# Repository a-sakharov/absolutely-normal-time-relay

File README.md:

# Очень лабораторный таймер

Все это к статье https://habr.com/ru/articles/726276/

 - firmware - прошивка MCS-48 (листинг, исходник, HEX)
 - schematics - схема самого таймера (без трассировки, конечно)
 - schematics_programmer - схема прошивальщика (есть непроверенные изменения!)

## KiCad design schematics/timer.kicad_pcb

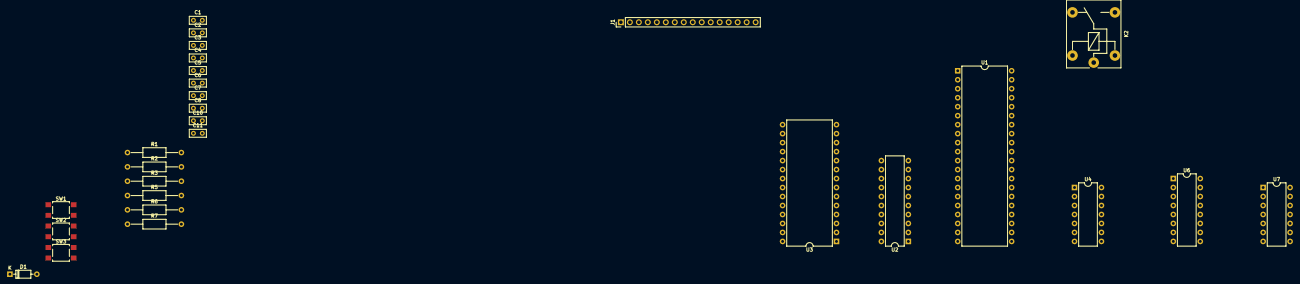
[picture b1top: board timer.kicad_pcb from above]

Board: 2 copper layers, 28 parts (0 on the bottom side), 44 nets, no tracks yet.

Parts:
C1, C2, C3, C4, C5, C6, C7, C8, C10, C11: 1uF; C_Rect_L4.6mm_W2.0mm_P2.50mm_MKS02_FKP02
D1: 1N4148; D_DO-35_SOD27_P7.62mm_Horizontal
J1: Conn_01x16_Pin; PinHeader_1x16_P2.54mm_Vertical
K2: FINDER-36.11; Relay_SPDT_Finder_36.11
R1, R2, R3, R5, R6, R7: 4.7k; R_Axial_DIN0207_L6.3mm_D2.5mm_P15.24mm_Horizontal
SW1, SW2, SW3: SW_Push; SW_SPST_TL3305C
U1: 8035; DIP-40_W15.24mm
U2: 74LS377; DIP-20_W7.62mm
U3: DIP-28_W15.24mm
U4: 74HC14; DIP-14_W7.62mm
U6: 4043; DIP-16_W7.62mm
U7: 4013; DIP-14_W7.62mm

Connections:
+5V: C2.2, C3.1, C4.1, C7.1, C8.2, J1.2, J1.15, R1.1, R2.2, R3.2, U1.7 (EA), U1.26 (VDD), U1.40 (VCC), U2.20 (VCC), U3.27 (~WE), U3.28 (VCC), U4.14 (VCC), U6.5 (EN), U6.16 (Vdd), U7.5 (D), U7.14 (VDD)
/ADDR8: U1.21 (P2.0), U3.25 (A8)
/ADDR9: U1.22 (P2.1), U3.24 (A9)
/ADDR10: U1.23 (P2.2), U3.21 (A10)
/ADDR11: U1.24 (P2.3), U3.23 (A11)
/ADDR_DATA0: U1.12 (DB.0), U2.3 (D0), U3.11 (D0)
/ADDR_DATA1: U1.13 (DB.1), U2.4 (D1), U3.12 (D1)
/ADDR_DATA2: U1.14 (DB.2), U2.7 (D2), U3.13 (D2)
/ADDR_DATA3: U1.15 (DB.3), U2.8 (D3), U3.15 (D3)
/ADDR_DATA4: U1.16 (DB.4), U2.13 (D4), U3.16 (D4)
/ADDR_DATA5: U1.17 (DB.5), U2.14 (D5), U3.17 (D5)
/ADDR_DATA6: U1.18 (DB.6), U2.17 (D6), U3.18 (D6)
/ADDR_DATA7: U1.19 (DB.7), U2.18 (D7), U3.19 (D7)
/ALE: U1.11 (ALE), U4.1
/BTN1: U1.1 (T0), U4.6
/BTN2: U1.39 (T1), U4.4
/DISP_D4: J1.11, U1.27 (P1.0)
/DISP_D5: J1.12, U1.28 (P1.1)
/DISP_D6: J1.13, U1.29 (P1.2)
/DISP_D7: J1.14, U1.30 (P1.3)
/DISP_E: J1.6, U1.32 (P1.5)
/DISP_RS: J1.4, U1.31 (P1.4)
/PSEN: U1.9 (~PSEN), U3.22 (~OE)
/SS: U1.5 (~SS), U7.1 (Q)
/SS_BTN: U6.2, U7.3 (C)
/nALE: U2.11 (CP), U4.2, U7.4 (R)
GND: C1.1, C2.1, C3.2, C4.2, C5.1, C6.1, C7.2, C8.1, C10.2, C11.2, D1.2 (A), J1.1, J1.5, J1.7, J1.8, J1.9, J1.10, J1.16, K2.A1, R5.2, R6.2, R7.2, SW1.1, SW2.1, SW3.1, U1.20 (GND), U2.1 (~E), U2.10 (GND), U3.2 (A12), U3.14 (GND), U3.20 (~CE), U4.7 (GND), U6.8 (Vss), U7.7 (VSS)
unnamed: C10.1, R2.1, SW1.2, U4.5
unnamed: C11.1, R3.1, SW3.2, U4.3
unnamed: D1.1 (K), K2.A2
unnamed: R5.1, U6.3
unnamed: R6.1, U6.4
unnamed: C5.2, U1.2 (X1)
unnamed: C6.2, U1.3 (X2)
unnamed: C1.2, R1.2, SW2.2, U1.4 (~RESET)
unnamed: U2.2 (Q0), U3.10 (A0)
unnamed: U2.5 (Q1), U3.9 (A1)
unnamed: U2.6 (Q2), U3.8 (A2)
unnamed: U2.9 (Q3), U3.7 (A3)
unnamed: U2.12 (Q4), U3.6 (A4)
unnamed: U2.15 (Q5), U3.5 (A5)
unnamed: U2.16 (Q6), U3.4 (A6)
unnamed: U2.19 (Q7), U3.3 (A7)
unnamed: R7.1, U7.6 (S)

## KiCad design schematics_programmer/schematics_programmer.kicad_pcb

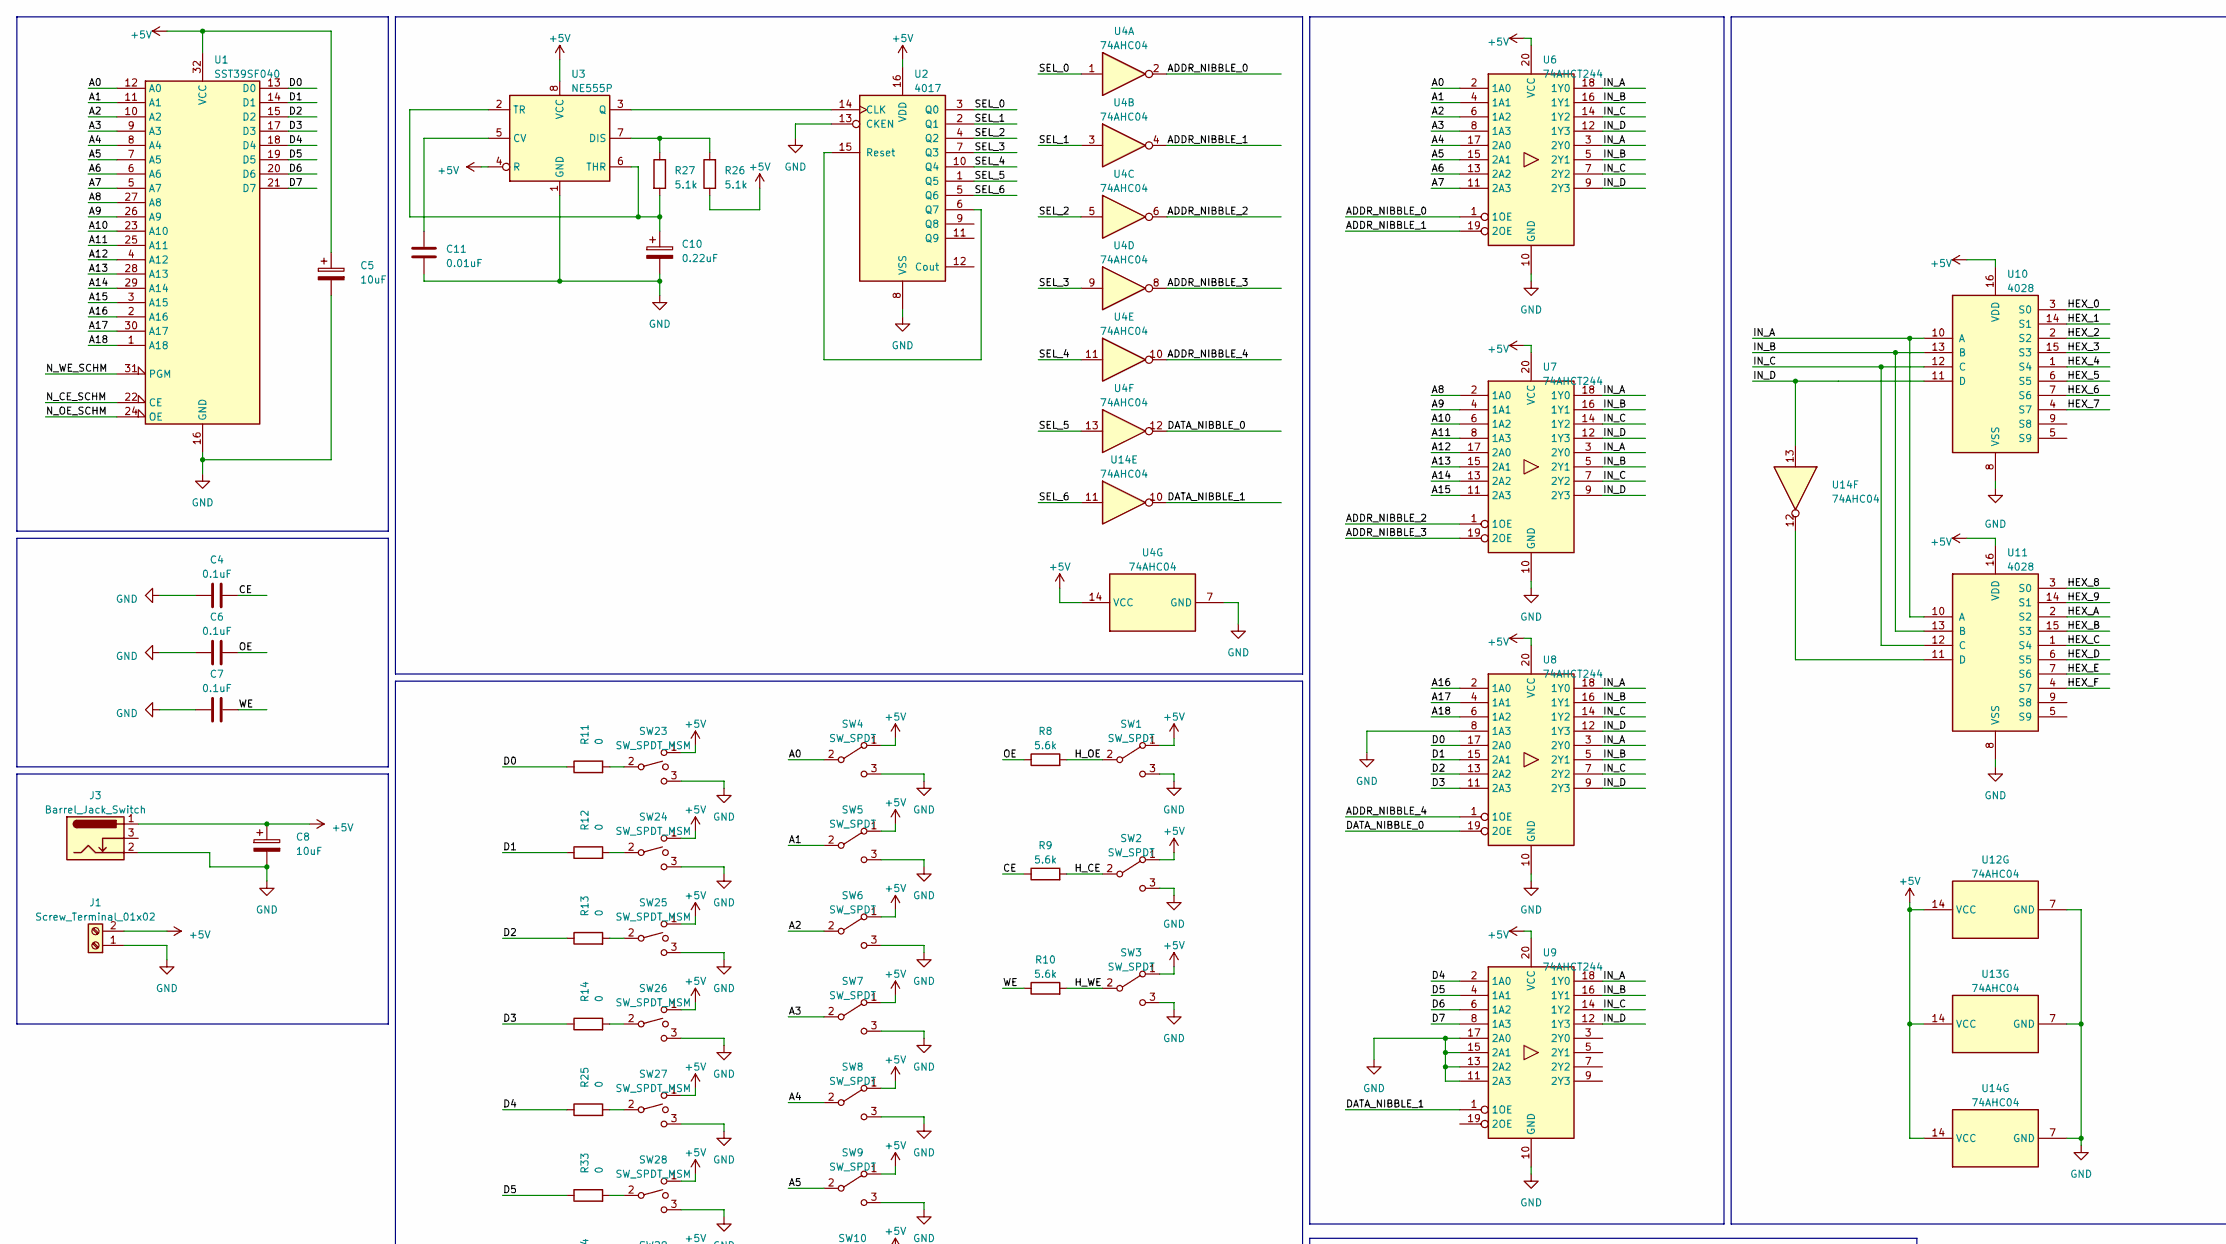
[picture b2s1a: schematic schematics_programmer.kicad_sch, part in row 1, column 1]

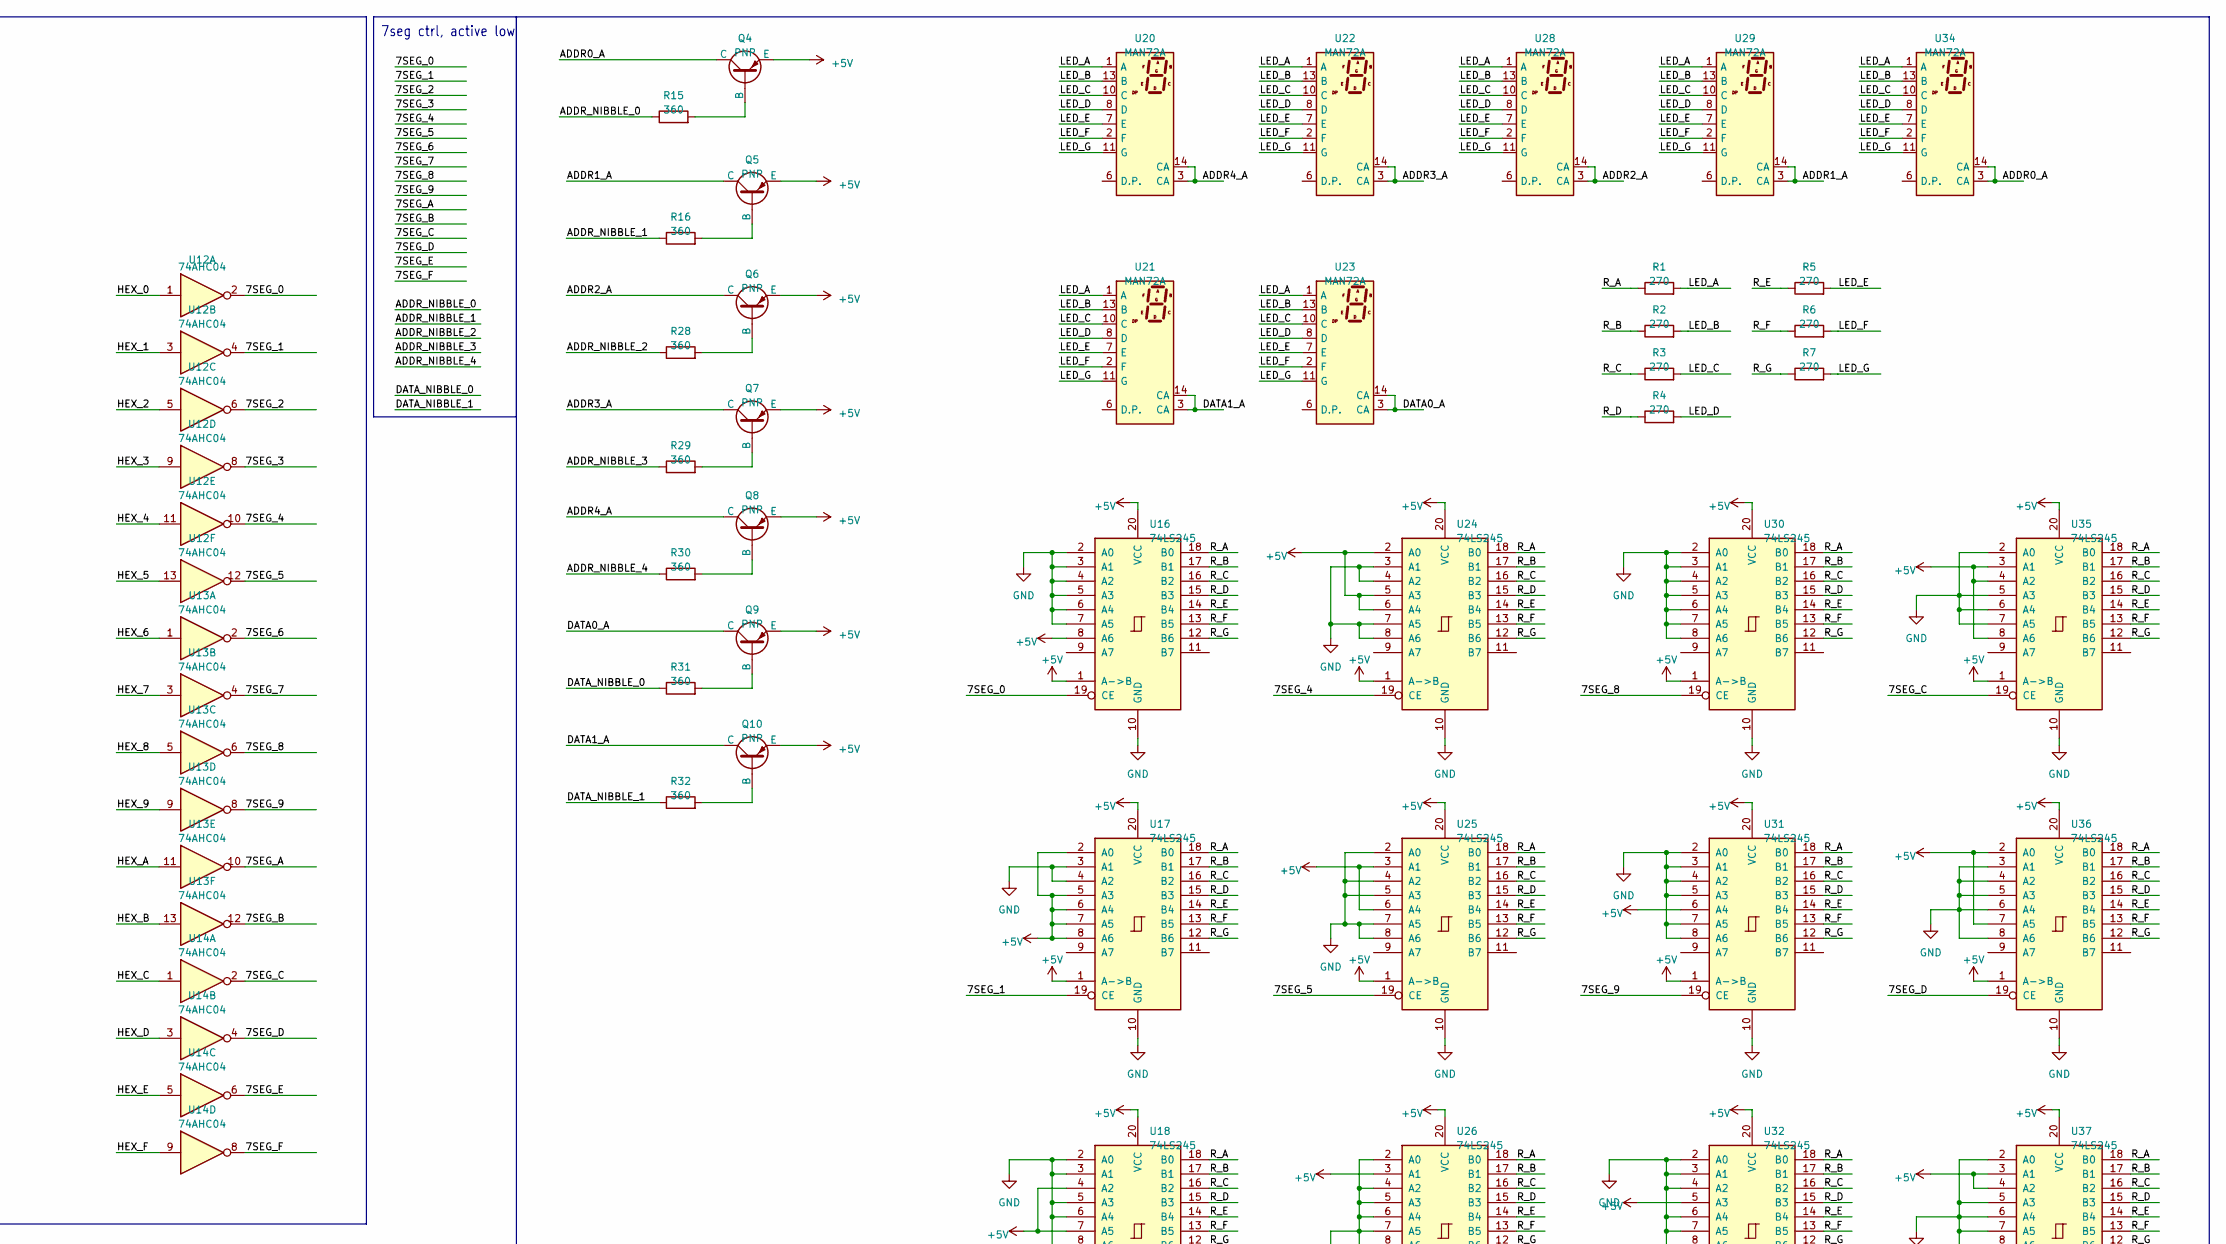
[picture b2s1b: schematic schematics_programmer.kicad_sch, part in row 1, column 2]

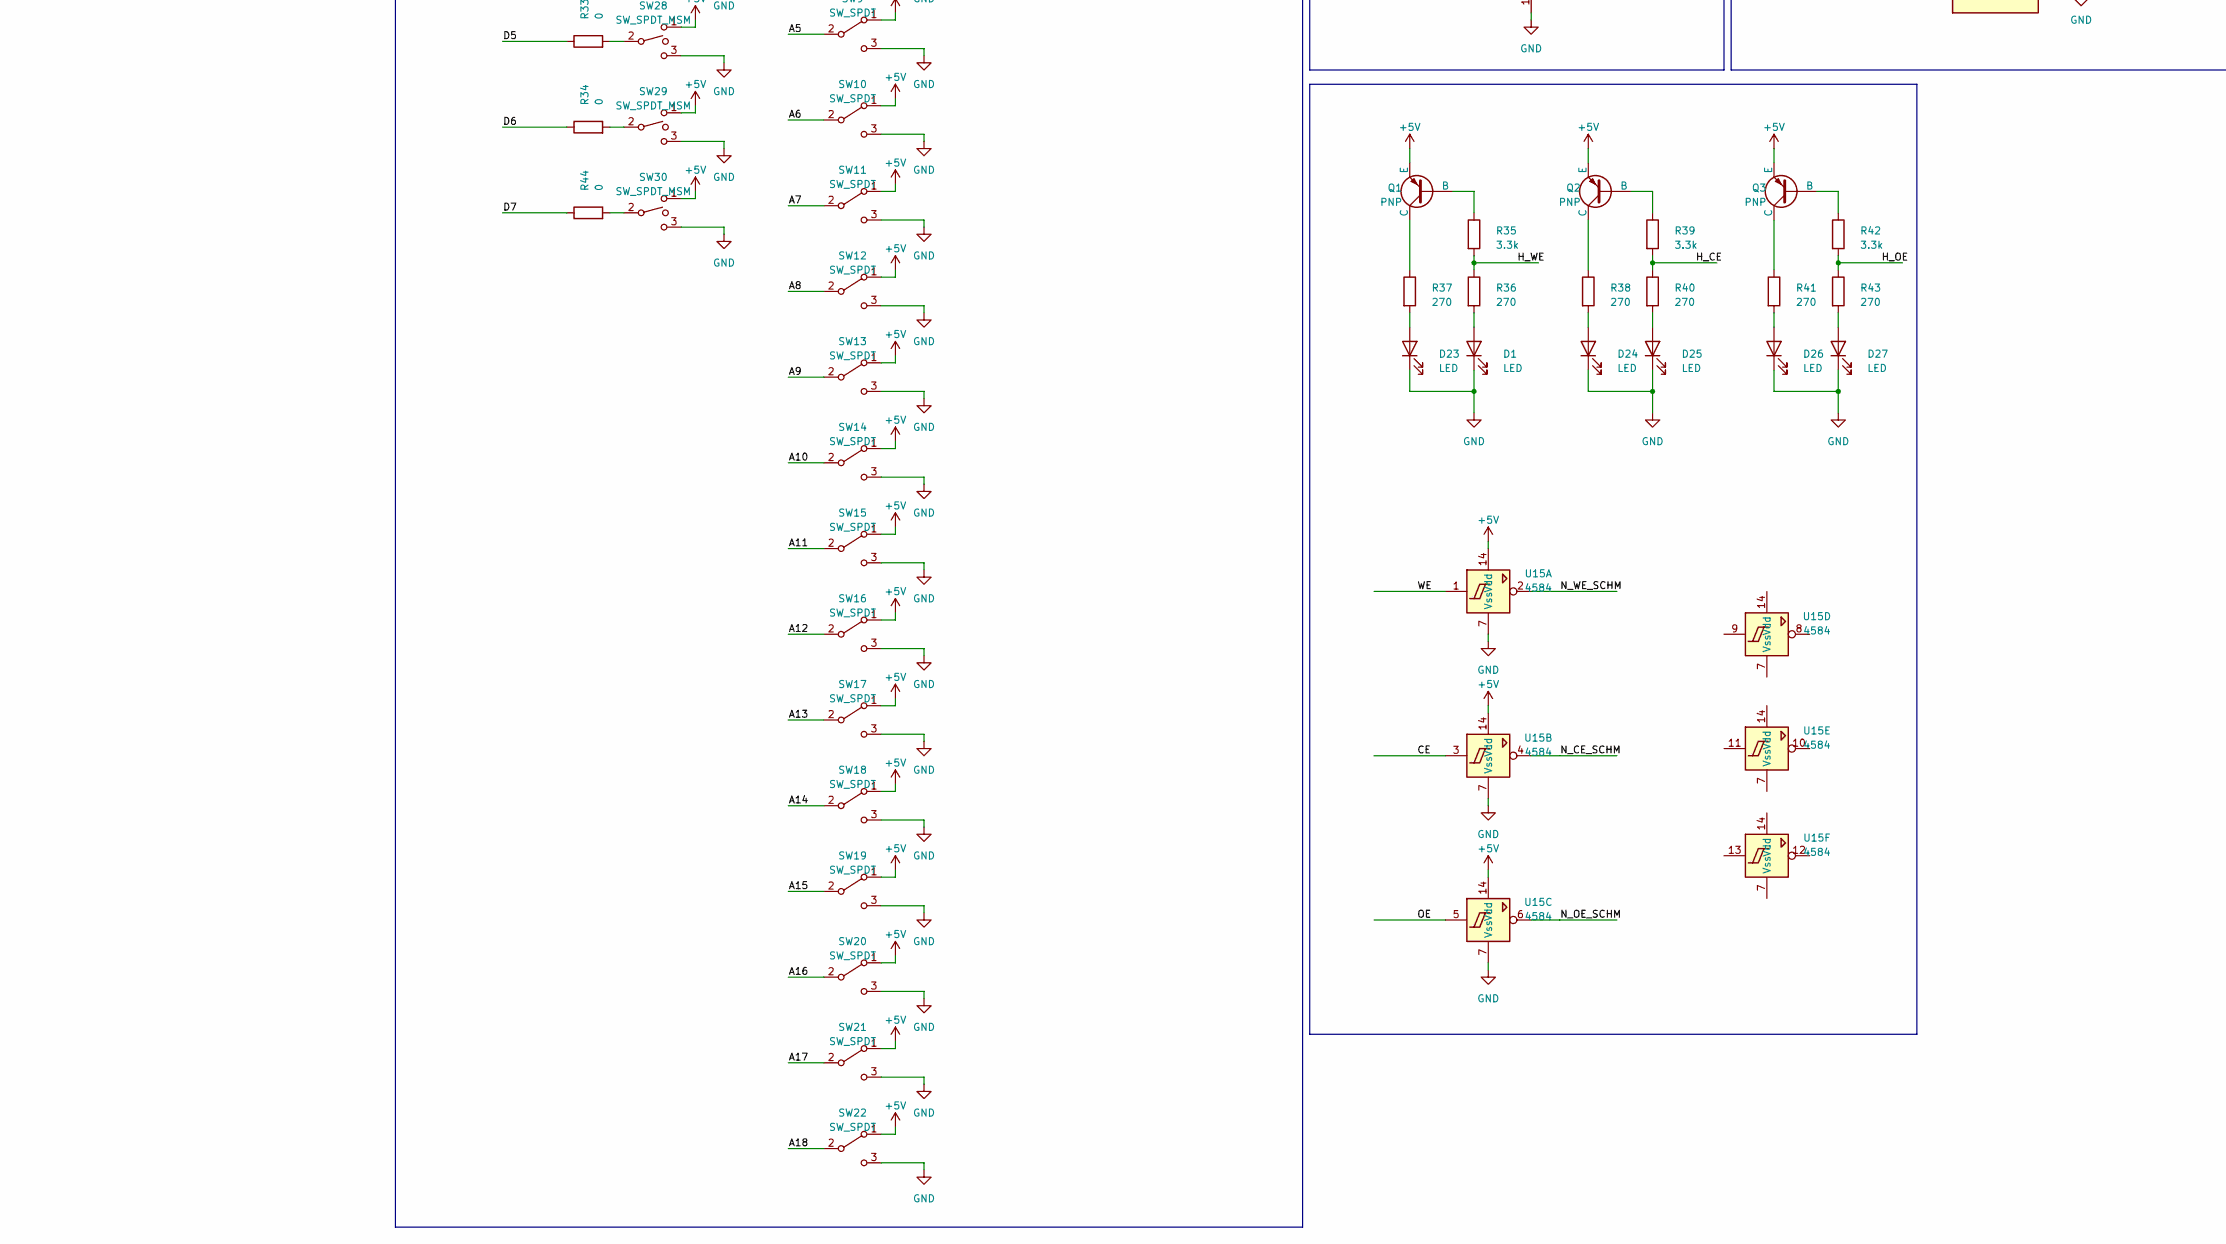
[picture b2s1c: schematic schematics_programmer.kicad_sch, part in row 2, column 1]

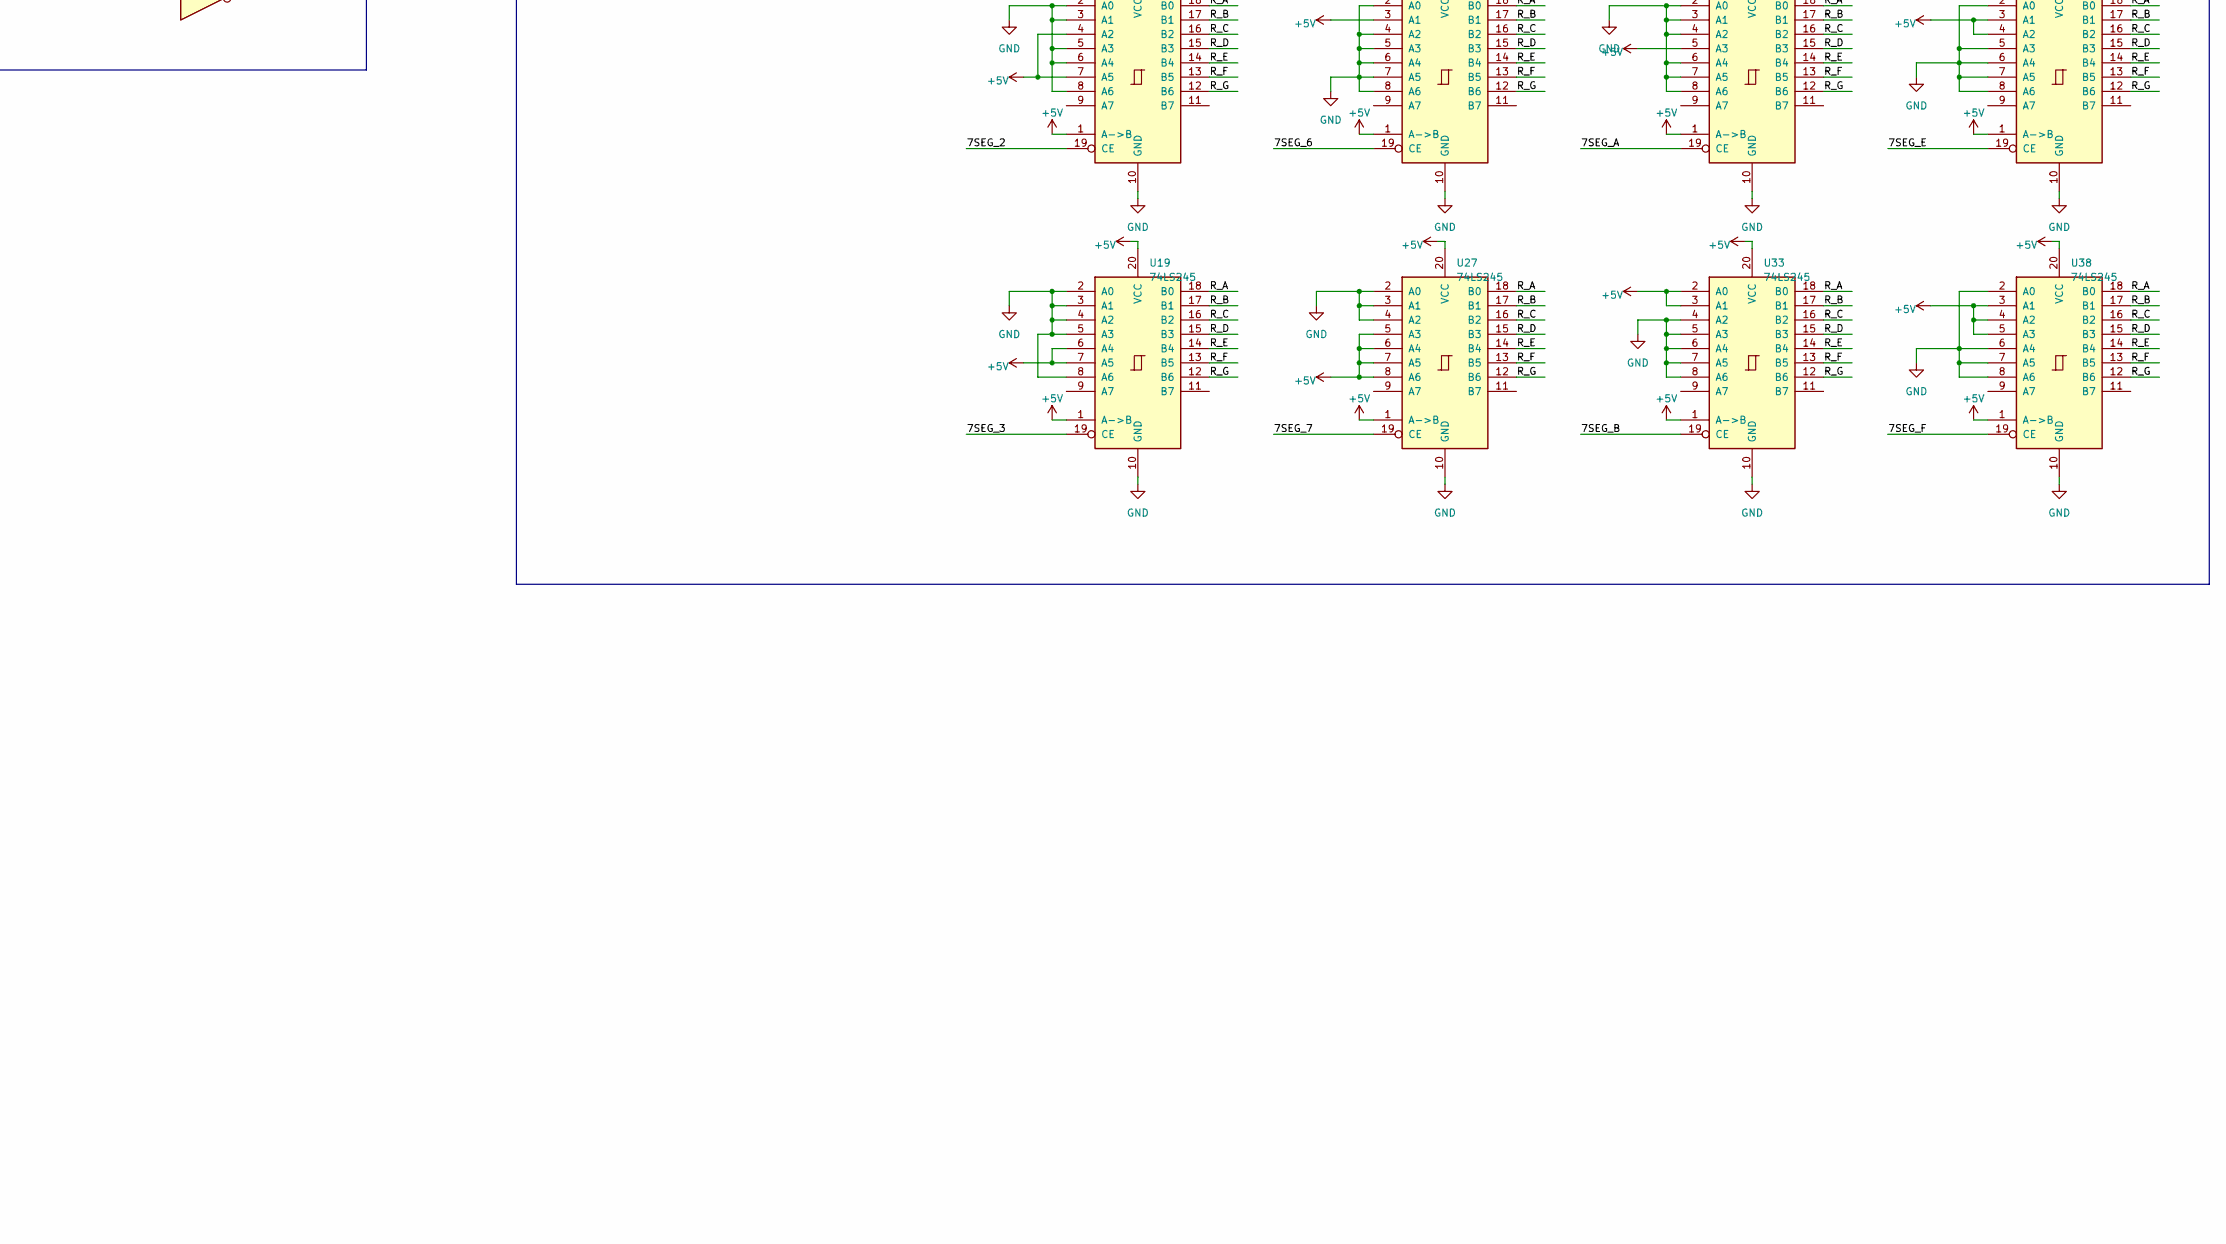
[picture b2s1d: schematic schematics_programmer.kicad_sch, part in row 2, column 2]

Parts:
C4, C6, C7: 0.1uF; C_Rect_L4.6mm_W2.0mm_P2.50mm_MKS02_FKP02
C5: 10uF; CP_Radial_D6.3mm_P2.50mm
C8: 10uF; CP_Radial_D5.0mm_P2.50mm
C10: 0.22uF; CP_Radial_D5.0mm_P2.50mm
C11: 0.01uF; C_Rect_L4.6mm_W2.0mm_P2.50mm_MKS02_FKP02
D1, D23, D24, D25, D26, D27: LED; LED_D3.0mm_Clear
J1: Screw_Terminal_01x02; TerminalBlock_Altech_AK300-2_P5.00mm
J3: Barrel_Jack_Switch; BarrelJack_GCT_DCJ200-10-A_Horizontal
Q1, Q2, Q3, Q4, Q5, Q6, Q7, Q8, Q9, Q10: PNP; TO-92
R1, R2, R3, R4, R5, R6, R7, R36, R37, R38, R40, R41, R43: 270; R_Axial_DIN0207_L6.3mm_D2.5mm_P15.24mm_Horizontal
R8, R9, R10: 5.6k; R_Axial_DIN0207_L6.3mm_D2.5mm_P15.24mm_Horizontal
R11, R12, R13, R14, R25, R33, R34, R44: 0; R_Axial_DIN0207_L6.3mm_D2.5mm_P15.24mm_Horizontal
R15, R16, R28, R29, R30, R31, R32: 360; R_Axial_DIN0207_L6.3mm_D2.5mm_P15.24mm_Horizontal
R26, R27: 5.1k; R_Axial_DIN0207_L6.3mm_D2.5mm_P15.24mm_Horizontal
R35, R39, R42: 3.3k; R_Axial_DIN0207_L6.3mm_D2.5mm_P15.24mm_Horizontal
SW1, SW2, SW3, SW4, SW5, SW6, SW7, SW8, SW9, SW10, SW11, SW12, SW13, SW14, SW15, SW16, SW17, SW18, SW19, SW20, SW21, SW22: SW_SPDT; MTS-102-A2
SW23, SW24, SW25, SW26, SW27, SW28, SW29, SW30: SW_SPDT_MSM; MTS-102-A2
U1: SST39SF040; DIP-32_W15.24mm
U2: 4017; DIP-16_W7.62mm
U3: NE555P; DIP-8_W7.62mm
U4, U12, U13, U14: 74AHC04; DIP-14_W7.62mm
U6, U7, U8, U9: 74AHCT244; DIP-20_W7.62mm
U10, U11: 4028; DIP-16_W7.62mm
U15: 4584; DIP-14_W7.62mm
U16, U17, U18, U19, U24, U25, U26, U27, U30, U31, U32, U33, U35, U36, U37, U38: 74LS245; DIP-20_W7.62mm
U20, U21, U22, U23, U28, U29, U34: MAN72A

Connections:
+5V: C5.1, C8.1, J1.2, J3.1, Q1.3 (E), Q2.3 (E), Q3.3 (E), Q4.3 (E), Q5.3 (E), Q6.3 (E), Q7.3 (E), Q8.3 (E), Q9.3 (E), Q10.3 (E), R26.1, SW1.1 (A), SW2.1 (A), SW3.1 (A), SW4.1 (A), SW5.1 (A), SW6.1 (A), SW7.1 (A), SW8.1 (A), SW9.1 (A), SW10.1 (A), SW11.1 (A), SW12.1 (A), SW13.1 (A), SW14.1 (A), SW15.1 (A), SW16.1 (A), SW17.1 (A), SW18.1 (A), SW19.1 (A), SW20.1 (A), SW21.1 (A), SW22.1 (A), SW23.1, SW24.1, SW25.1, SW26.1, SW27.1, SW28.1, SW29.1, SW30.1, U1.32 (VCC), U2.16 (VDD), U3.4 (R), U3.8 (VCC), U4.14 (VCC), U6.20 (VCC), U7.20 (VCC), U8.20 (VCC), U9.20 (VCC), U10.16 (VDD), U11.16 (VDD), U12.14 (VCC), U13.14 (VCC), U14.14 (VCC), U15.14 (Vdd), U16.1 (A->B), U16.8 (A6), U16.20 (VCC), U17.1 (A->B), U17.2 (A0), U17.5 (A3), U17.6 (A4), U17.7 (A5), U17.8 (A6), U17.20 (VCC), U18.1 (A->B), U18.4 (A2), U18.7 (A5), U18.20 (VCC), U19.1 (A->B), U19.6 (A4), U19.7 (A5), U19.20 (VCC), U24.1 (A->B), U24.2 (A0), U24.5 (A3), U24.6 (A4), U24.20 (VCC), U25.1 (A->B), U25.3 (A1), U25.6 (A4), U25.20 (VCC), U26.1 (A->B), U26.3 (A1), U26.20 (VCC), U27.1 (A->B), U27.5 (A3), U27.6 (A4), U27.7 (A5), U27.8 (A6), U27.20 (VCC), U30.1 (A->B), U30.20 (VCC), U31.1 (A->B), U31.6 (A4), U31.20 (VCC), U32.1 (A->B), U32.5 (A3), U32.20 (VCC), U33.1 (A->B), U33.2 (A0), U33.3 (A1), U33.20 (VCC), U35.1 (A->B), U35.3 (A1), U35.4 (A2), U35.8 (A6), U35.20 (VCC), U36.1 (A->B), U36.2 (A0), U36.7 (A5), U36.20 (VCC), U37.1 (A->B), U37.3 (A1), U37.4 (A2), U37.20 (VCC), U38.1 (A->B), U38.3 (A1), U38.4 (A2), U38.5 (A3), U38.20 (VCC)
/7SEG_0: U12.2, U16.19 (CE)
/7SEG_1: U12.4, U17.19 (CE)
/7SEG_2: U12.6, U18.19 (CE)
/7SEG_3: U12.8, U19.19 (CE)
/7SEG_4: U12.10, U24.19 (CE)
/7SEG_5: U12.12, U25.19 (CE)
/7SEG_6: U13.2, U26.19 (CE)
/7SEG_7: U13.4, U27.19 (CE)
/7SEG_8: U13.6, U30.19 (CE)
/7SEG_9: U13.8, U31.19 (CE)
/7SEG_A: U13.10, U32.19 (CE)
/7SEG_B: U13.12, U33.19 (CE)
/7SEG_C: U14.2, U35.19 (CE)
/7SEG_D: U14.4, U36.19 (CE)
/7SEG_E: U14.6, U37.19 (CE)
/7SEG_F: U14.8, U38.19 (CE)
/A0: SW4.2 (B), U1.12 (A0), U6.2 (1A0)
/A1: SW5.2 (B), U1.11 (A1), U6.4 (1A1)
/A2: SW6.2 (B), U1.10 (A2), U6.6 (1A2)
/A3: SW7.2 (B), U1.9 (A3), U6.8 (1A3)
/A4: SW8.2 (B), U1.8 (A4), U6.17 (2A0)
/A5: SW9.2 (B), U1.7 (A5), U6.15 (2A1)
/A6: SW10.2 (B), U1.6 (A6), U6.13 (2A2)
/A7: SW11.2 (B), U1.5 (A7), U6.11 (2A3)
/A8: SW12.2 (B), U1.27 (A8), U7.2 (1A0)
/A9: SW13.2 (B), U1.26 (A9), U7.4 (1A1)
/A10: SW14.2 (B), U1.23 (A10), U7.6 (1A2)
/A11: SW15.2 (B), U1.25 (A11), U7.8 (1A3)
/A12: SW16.2 (B), U1.4 (A12), U7.17 (2A0)
/A13: SW17.2 (B), U1.28 (A13), U7.15 (2A1)
/A14: SW18.2 (B), U1.29 (A14), U7.13 (2A2)
/A15: SW19.2 (B), U1.3 (A15), U7.11 (2A3)
/A16: SW20.2 (B), U1.2 (A16), U8.2 (1A0)
/A17: SW21.2 (B), U1.30 (A17), U8.4 (1A1)
/A18: SW22.2 (B), U1.1 (A18), U8.6 (1A2)
/ADDR0_A: Q4.1 (C), U34.3 (CA), U34.14 (CA)
/ADDR1_A: Q5.1 (C), U29.3 (CA), U29.14 (CA)
/ADDR2_A: Q6.1 (C), U28.3 (CA), U28.14 (CA)
/ADDR3_A: Q7.1 (C), U22.3 (CA), U22.14 (CA)
/ADDR4_A: Q8.1 (C), U20.3 (CA), U20.14 (CA)
/ADDR_NIBBLE_0: R15.1, U4.2, U6.1 (1OE)
/ADDR_NIBBLE_1: R16.1, U4.4, U6.19 (2OE)
/ADDR_NIBBLE_2: R28.1, U4.6, U7.1 (1OE)
/ADDR_NIBBLE_3: R29.1, U4.8, U7.19 (2OE)
/ADDR_NIBBLE_4: R30.1, U4.10, U8.1 (1OE)
/CE: C4.2, R9.1, U15.3
/D0: R11.1, U1.13 (D0), U8.17 (2A0)
/D1: R12.1, U1.14 (D1), U8.15 (2A1)
/D2: R13.1, U1.15 (D2), U8.13 (2A2)
/D3: R14.1, U1.17 (D3), U8.11 (2A3)
/D4: R25.1, U1.18 (D4), U9.2 (1A0)
/D5: R33.1, U1.19 (D5), U9.4 (1A1)
/D6: R34.1, U1.20 (D6), U9.6 (1A2)
/D7: R44.1, U1.21 (D7), U9.8 (1A3)
/DATA0_A: Q9.1 (C), U23.3 (CA), U23.14 (CA)
/DATA1_A: Q10.1 (C), U21.3 (CA), U21.14 (CA)
/DATA_NIBBLE_0: R31.1, U4.12, U8.19 (2OE)
/DATA_NIBBLE_1: R32.1, U9.1 (1OE), U14.10
/HEX_0: U10.3 (S0), U12.1
/HEX_1: U10.14 (S1), U12.3
/HEX_2: U10.2 (S2), U12.5
/HEX_3: U10.15 (S3), U12.9
/HEX_4: U10.1 (S4), U12.11
/HEX_5: U10.6 (S5), U12.13
/HEX_6: U10.7 (S6), U13.1
/HEX_7: U10.4 (S7), U13.3
/HEX_8: U11.3 (S0), U13.5
/HEX_9: U11.14 (S1), U13.9
/HEX_A: U11.2 (S2), U13.11
/HEX_B: U11.15 (S3), U13.13
/HEX_C: U11.1 (S4), U14.1
/HEX_D: U11.6 (S5), U14.3
/HEX_E: U11.7 (S6), U14.5
/HEX_F: U11.4 (S7), U14.9
/H_CE: R9.2, R39.2, R40.1, SW2.2 (B)
/H_OE: R8.2, R42.2, R43.1, SW1.2 (B)
/H_WE: R10.2, R35.2, R36.1, SW3.2 (B)
/IN_A: U6.3 (2Y0), U6.18 (1Y0), U7.3 (2Y0), U7.18 (1Y0), U8.3 (2Y0), U8.18 (1Y0), U9.18 (1Y0), U10.10 (A), U11.10 (A)
/IN_B: U6.5 (2Y1), U6.16 (1Y1), U7.5 (2Y1), U7.16 (1Y1), U8.5 (2Y1), U8.16 (1Y1), U9.16 (1Y1), U10.13 (B), U11.13 (B)
/IN_C: U6.7 (2Y2), U6.14 (1Y2), U7.7 (2Y2), U7.14 (1Y2), U8.7 (2Y2), U8.14 (1Y2), U9.14 (1Y2), U10.12 (C), U11.12 (C)
/IN_D: U6.9 (2Y3), U6.12 (1Y3), U7.9 (2Y3), U7.12 (1Y3), U8.9 (2Y3), U8.12 (1Y3), U9.12 (1Y3), U10.11 (D), U14.13
/LED_A: R1.2, U20.1 (A), U21.1 (A), U22.1 (A), U23.1 (A), U28.1 (A), U29.1 (A), U34.1 (A)
/LED_B: R2.2, U20.13 (B), U21.13 (B), U22.13 (B), U23.13 (B), U28.13 (B), U29.13 (B), U34.13 (B)
/LED_C: R3.2, U20.10 (C), U21.10 (C), U22.10 (C), U23.10 (C), U28.10 (C), U29.10 (C), U34.10 (C)
/LED_D: R4.2, U20.8 (D), U21.8 (D), U22.8 (D), U23.8 (D), U28.8 (D), U29.8 (D), U34.8 (D)
/LED_E: R5.2, U20.7 (E), U21.7 (E), U22.7 (E), U23.7 (E), U28.7 (E), U29.7 (E), U34.7 (E)
/LED_F: R6.2, U20.2 (F), U21.2 (F), U22.2 (F), U23.2 (F), U28.2 (F), U29.2 (F), U34.2 (F)
/LED_G: R7.2, U20.11 (G), U21.11 (G), U22.11 (G), U23.11 (G), U28.11 (G), U29.11 (G), U34.11 (G)
/N_CE_SCHM: U1.22 (CE), U15.4
/N_OE_SCHM: U1.24 (OE), U15.6
/N_WE_SCHM: U1.31 (PGM), U15.2
/OE: C6.2, R8.1, U15.5
/R_A: R1.1, U16.18 (B0), U17.18 (B0), U18.18 (B0), U19.18 (B0), U24.18 (B0), U25.18 (B0), U26.18 (B0), U27.18 (B0), U30.18 (B0), U31.18 (B0), U32.18 (B0), U33.18 (B0), U35.18 (B0), U36.18 (B0), U37.18 (B0), U38.18 (B0)
/R_B: R2.1, U16.17 (B1), U17.17 (B1), U18.17 (B1), U19.17 (B1), U24.17 (B1), U25.17 (B1), U26.17 (B1), U27.17 (B1), U30.17 (B1), U31.17 (B1), U32.17 (B1), U33.17 (B1), U35.17 (B1), U36.17 (B1), U37.17 (B1), U38.17 (B1)
/R_C: R3.1, U16.16 (B2), U17.16 (B2), U18.16 (B2), U19.16 (B2), U24.16 (B2), U25.16 (B2), U26.16 (B2), U27.16 (B2), U30.16 (B2), U31.16 (B2), U32.16 (B2), U33.16 (B2), U35.16 (B2), U36.16 (B2), U37.16 (B2), U38.16 (B2)
/R_D: R4.1, U16.15 (B3), U17.15 (B3), U18.15 (B3), U19.15 (B3), U24.15 (B3), U25.15 (B3), U26.15 (B3), U27.15 (B3), U30.15 (B3), U31.15 (B3), U32.15 (B3), U33.15 (B3), U35.15 (B3), U36.15 (B3), U37.15 (B3), U38.15 (B3)
/R_E: R5.1, U16.14 (B4), U17.14 (B4), U18.14 (B4), U19.14 (B4), U24.14 (B4), U25.14 (B4), U26.14 (B4), U27.14 (B4), U30.14 (B4), U31.14 (B4), U32.14 (B4), U33.14 (B4), U35.14 (B4), U36.14 (B4), U37.14 (B4), U38.14 (B4)
/R_F: R6.1, U16.13 (B5), U17.13 (B5), U18.13 (B5), U19.13 (B5), U24.13 (B5), U25.13 (B5), U26.13 (B5), U27.13 (B5), U30.13 (B5), U31.13 (B5), U32.13 (B5), U33.13 (B5), U35.13 (B5), U36.13 (B5), U37.13 (B5), U38.13 (B5)
/R_G: R7.1, U16.12 (B6), U17.12 (B6), U18.12 (B6), U19.12 (B6), U24.12 (B6), U25.12 (B6), U26.12 (B6), U27.12 (B6), U30.12 (B6), U31.12 (B6), U32.12 (B6), U33.12 (B6), U35.12 (B6), U36.12 (B6), U37.12 (B6), U38.12 (B6)
/SEL_0: U2.3 (Q0), U4.1
/SEL_1: U2.2 (Q1), U4.3
/SEL_2: U2.4 (Q2), U4.5
/SEL_3: U2.7 (Q3), U4.9
/SEL_4: U2.10 (Q4), U4.11
/SEL_5: U2.1 (Q5), U4.13
/SEL_6: U2.5 (Q6), U14.11
/WE: C7.2, R10.1, U15.1
GND: C4.1, C5.2, C6.1, C7.1, C8.2, C10.2, C11.2, D1.1 (K), D23.1 (K), D24.1 (K), D25.1 (K), D26.1 (K), D27.1 (K), J1.1, J3.2, SW1.3 (C), SW2.3 (C), SW3.3 (C), SW4.3 (C), SW5.3 (C), SW6.3 (C), SW7.3 (C), SW8.3 (C), SW9.3 (C), SW10.3 (C), SW11.3 (C), SW12.3 (C), SW13.3 (C), SW14.3 (C), SW15.3 (C), SW16.3 (C), SW17.3 (C), SW18.3 (C), SW19.3 (C), SW20.3 (C), SW21.3 (C), SW22.3 (C), SW23.3, SW24.3, SW25.3, SW26.3, SW27.3, SW28.3, SW29.3, SW30.3, U1.16 (GND), U2.8 (VSS), U2.13 (CKEN), U3.1 (GND), U4.7 (GND), U6.10 (GND), U7.10 (GND), U8.8 (1A3), U8.10 (GND), U9.10 (GND), U9.11 (2A3), U9.13 (2A2), U9.15 (2A1), U9.17 (2A0), U10.8 (VSS), U11.8 (VSS), U12.7 (GND), U13.7 (GND), U14.7 (GND), U15.7 (Vss), U16.2 (A0), U16.3 (A1), U16.4 (A2), U16.5 (A3), U16.6 (A4), U16.7 (A5), U16.10 (GND), U17.3 (A1), U17.4 (A2), U17.10 (GND), U18.2 (A0), U18.3 (A1), U18.5 (A3), U18.6 (A4), U18.8 (A6), U18.10 (GND), U19.2 (A0), U19.3 (A1), U19.4 (A2), U19.5 (A3), U19.8 (A6), U19.10 (GND), U24.3 (A1), U24.4 (A2), U24.7 (A5), U24.8 (A6), U24.10 (GND), U25.2 (A0), U25.4 (A2), U25.5 (A3), U25.7 (A5), U25.8 (A6), U25.10 (GND), U26.2 (A0), U26.4 (A2), U26.5 (A3), U26.6 (A4), U26.7 (A5), U26.8 (A6), U26.10 (GND), U27.2 (A0), U27.3 (A1), U27.4 (A2), U27.10 (GND), U30.2 (A0), U30.3 (A1), U30.4 (A2), U30.5 (A3), U30.6 (A4), U30.7 (A5), U30.8 (A6), U30.10 (GND), U31.2 (A0), U31.3 (A1), U31.4 (A2), U31.5 (A3), U31.7 (A5), U31.8 (A6), U31.10 (GND), U32.2 (A0), U32.3 (A1), U32.4 (A2), U32.6 (A4), U32.7 (A5), U32.8 (A6), U32.10 (GND), U33.4 (A2), U33.5 (A3), U33.6 (A4), U33.7 (A5), U33.8 (A6), U33.10 (GND), U35.2 (A0), U35.5 (A3), U35.6 (A4), U35.7 (A5), U35.10 (GND), U36.3 (A1), U36.4 (A2), U36.5 (A3), U36.6 (A4), U36.8 (A6), U36.10 (GND), U37.2 (A0), U37.5 (A3), U37.6 (A4), U37.7 (A5), U37.8 (A6), U37.10 (GND), U38.2 (A0), U38.6 (A4), U38.7 (A5), U38.8 (A6), U38.10 (GND)
unnamed: D1.2 (A), R36.2
unnamed: D23.2 (A), R37.2
unnamed: D24.2 (A), R38.2
unnamed: D25.2 (A), R40.2
unnamed: D26.2 (A), R41.2
unnamed: D27.2 (A), R43.2
unnamed: Q1.2 (B), R35.1
unnamed: Q1.1 (C), R37.1
unnamed: Q2.2 (B), R39.1
unnamed: Q2.1 (C), R38.1
unnamed: Q3.2 (B), R42.1
unnamed: Q3.1 (C), R41.1
unnamed: Q4.2 (B), R15.2
unnamed: Q5.2 (B), R16.2
unnamed: Q6.2 (B), R28.2
unnamed: Q7.2 (B), R29.2
unnamed: Q8.2 (B), R30.2
unnamed: Q9.2 (B), R31.2
unnamed: Q10.2 (B), R32.2
unnamed: R11.2, SW23.2
unnamed: R12.2, SW24.2
unnamed: R13.2, SW25.2
unnamed: R14.2, SW26.2
unnamed: R25.2, SW27.2
unnamed: R33.2, SW28.2
unnamed: R34.2, SW29.2
unnamed: R44.2, SW30.2
unnamed: U2.14 (CLK), U3.3 (Q)
unnamed: U2.6 (Q7), U2.15 (Reset)
unnamed: C11.1, U3.5 (CV)
unnamed: R26.2, R27.1, U3.7 (DIS)
unnamed: C10.1, R27.2, U3.2 (TR), U3.6 (THR)
unnamed: U11.11 (D), U14.12

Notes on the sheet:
7seg ctrl, active low

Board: 2 copper layers, 128 parts (0 on the bottom side), 142 nets, no tracks yet.

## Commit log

2023-04-01 Initial commit (already working)
2023-04-01 Added empty readme.md
